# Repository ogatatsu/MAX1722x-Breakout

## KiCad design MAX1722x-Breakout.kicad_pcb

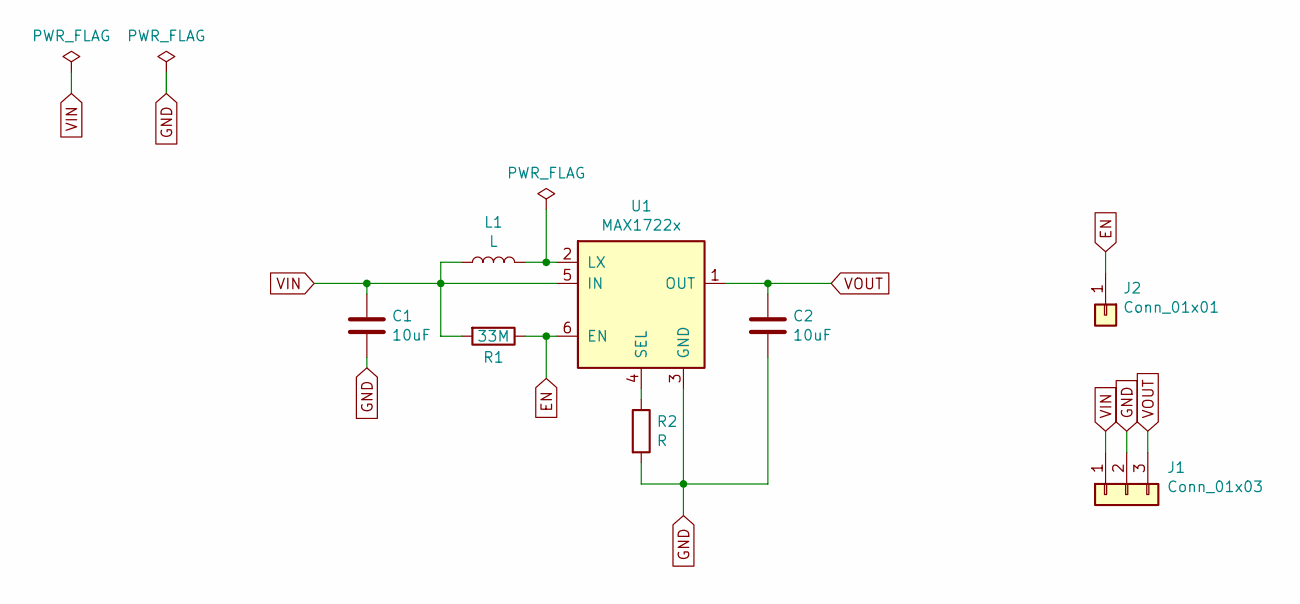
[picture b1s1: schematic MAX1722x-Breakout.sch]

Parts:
C1, C2: 10uF; C_0603_1608Metric
J1: Conn_01x03; Connector_2.54mm_03
J2: Conn_01x01; Connector_2.54mm_01
L1: L; L_0805_2012Metric
R1: 33M; R_0603_1608Metric
R2: R; R_0603_1608Metric
U1: MAX1722x; uDFN-6

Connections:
EN: J2.1, R1.1, U1.6 (EN)
GND: C1.2, C2.2, J1.2, R2.2, U1.3 (GND)
unnamed: L1.2, U1.2 (LX)
unnamed: R2.1, U1.4 (SEL)
VIN: C1.1, J1.1, L1.1, R1.2, U1.5 (IN)
VOUT: C2.1, J1.3, U1.1 (OUT)

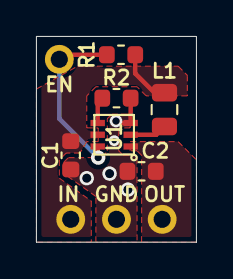
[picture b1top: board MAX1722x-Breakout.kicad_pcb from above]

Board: 2 copper layers, 8.9 x 11.4 mm, 8 parts (0 on the bottom side), 6 nets.

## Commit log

2020-11-08 add schematic
